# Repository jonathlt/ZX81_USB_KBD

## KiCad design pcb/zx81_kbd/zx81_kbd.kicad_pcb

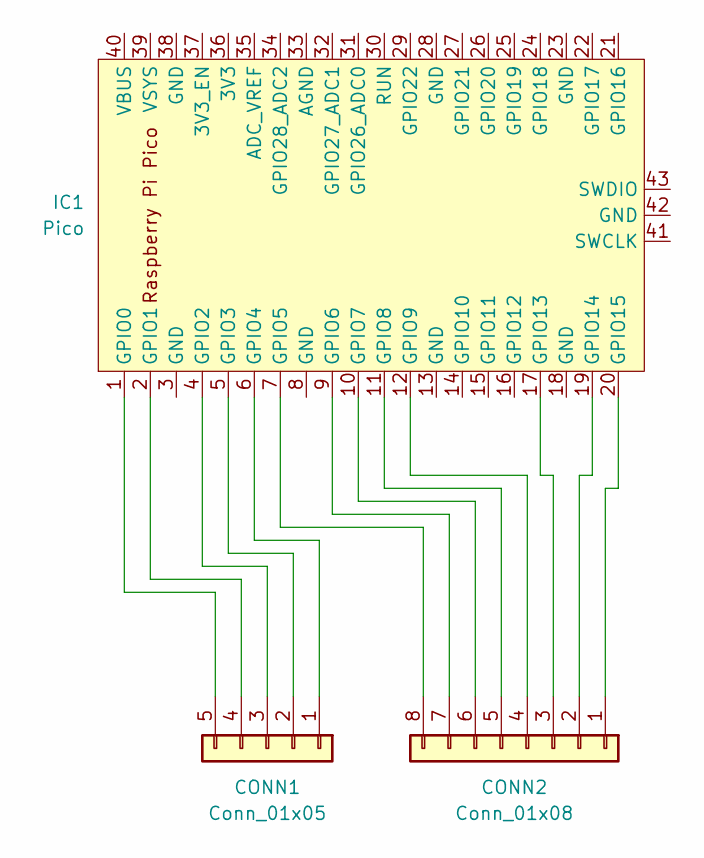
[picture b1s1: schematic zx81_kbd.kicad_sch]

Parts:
CONN1: Conn_01x05; PinHeader_1x05_P2.54mm_Vertical
CONN2: Conn_01x08; PinHeader_1x08_P2.54mm_Vertical
IC1: Pico; RPi_Pico_SMD_TH

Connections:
unnamed: CONN1.5, IC1.1 (GPIO0)
unnamed: CONN1.4, IC1.2 (GPIO1)
unnamed: CONN1.3, IC1.4 (GPIO2)
unnamed: CONN1.2, IC1.5 (GPIO3)
unnamed: CONN1.1, IC1.6 (GPIO4)
unnamed: CONN2.8, IC1.7 (GPIO5)
unnamed: CONN2.7, IC1.9 (GPIO6)
unnamed: CONN2.6, IC1.10 (GPIO7)
unnamed: CONN2.5, IC1.11 (GPIO8)
unnamed: CONN2.4, IC1.12 (GPIO9)
unnamed: CONN2.3, IC1.17 (GPIO13)
unnamed: CONN2.2, IC1.19 (GPIO14)
unnamed: CONN2.1, IC1.20 (GPIO15)

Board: 2 copper layers, 3 parts (0 on the bottom side), 13 nets, no tracks yet.

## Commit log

2024-02-24 Changed to work with tynemouth software minstrel keyboard
2024-10-28 Found code common to 2 boards
2024-11-09 ZX81 membrane pcb added
